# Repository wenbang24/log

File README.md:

# Log
A low-profile, wireless, portable rendition of the OLKB Planck keyboard.

# Firmware
Log uses [ZMK](https://zmk.dev/) for its firmware. The firmware is available in the `zmk-keyboard-log` sub-repo.

# BOM
| Part | Quantity | Price | Link |
| ---- | -------- | ----- | ---- |
| Supermini nRF52840 | 1 | $4.45 | [AliExpress](https://www.aliexpress.com/item/1005007205026373.html) |
| Kailh Choc V1 | 48 | $21.77 | [AliExpress](https://www.aliexpress.com/item/1005004106505158.html) |
| 1N4148 Diode | 48 | included in PCB cost | [AliExpress](https://www.aliexpress.com/item/1005003208856262.html) |
| CFX Keycap Set | 1 | $27.76 | [AliExpress](https://www.aliexpress.com/item/1005005291084816.html) |
| M2x3 Heat-Set Inserts | 4 | $1.60 | [AliExpress](https://www.aliexpress.com/item/1005003582355741.html) |
| M2 Flat Head Screws 5mm | 4 | $1.25 | [AliExpress](https://www.aliexpress.com/item/1005008691176275.html) |
| 3.7V 5000mAh Battery | 1 | $9.64 | [AliExpress](https://www.aliexpress.com/item/1005006877616182.html) |

Total: $67.83

(prices converted from AUD to USD, as of 2025-07-16)

PCB & PCBA cost: $29.34

**TOTAL: $97.17**

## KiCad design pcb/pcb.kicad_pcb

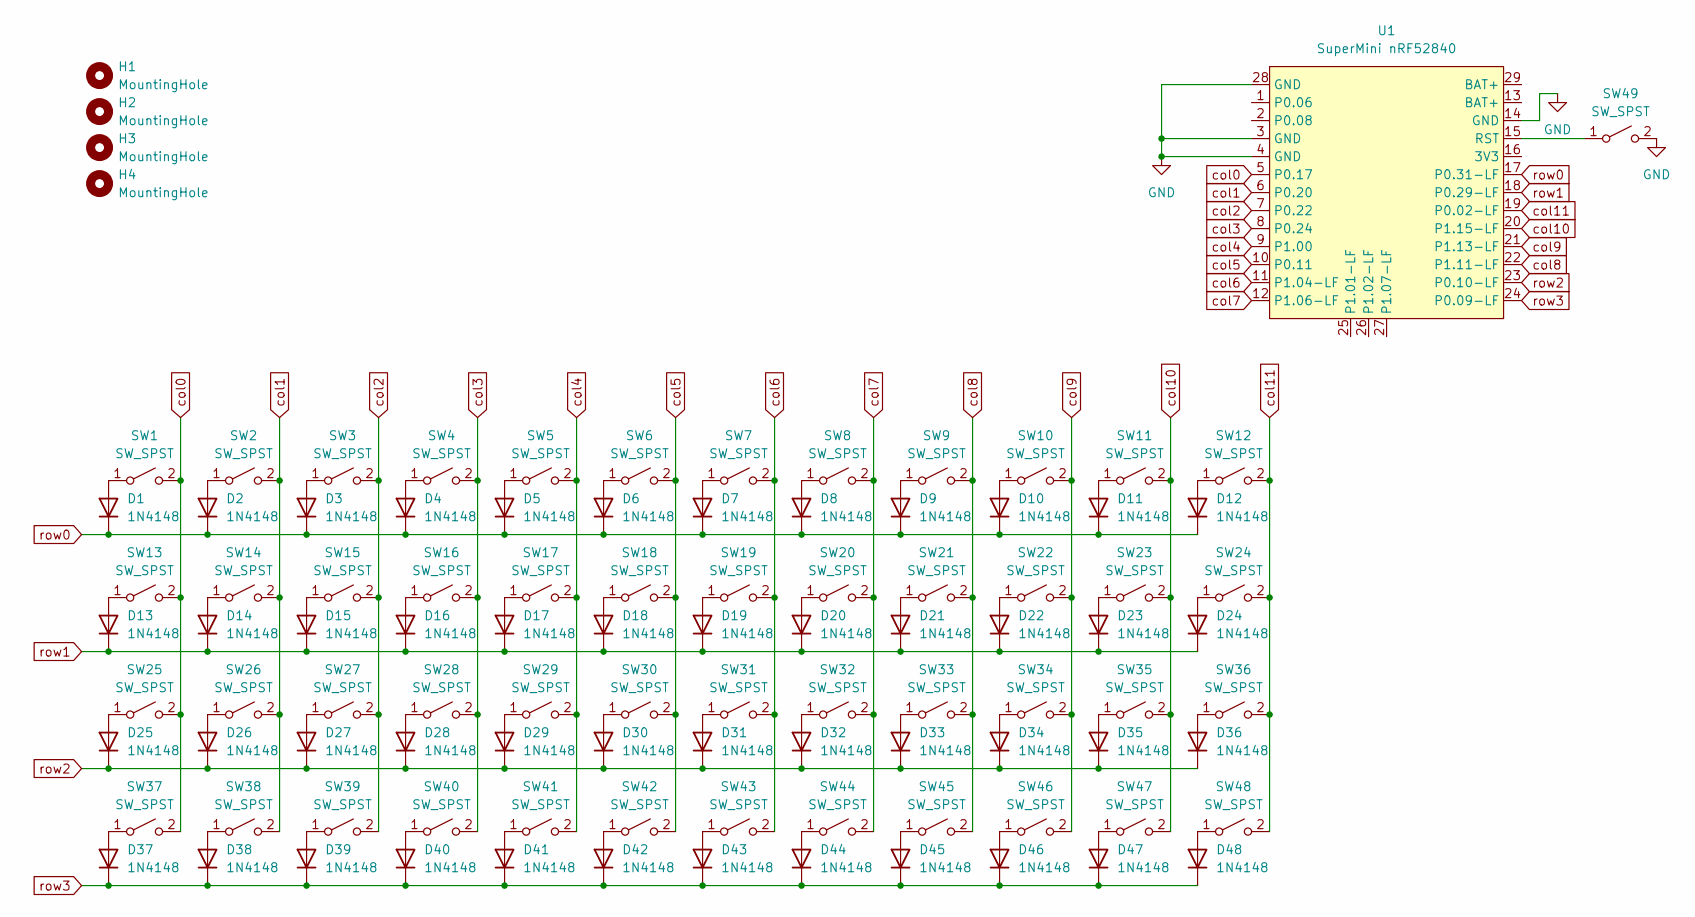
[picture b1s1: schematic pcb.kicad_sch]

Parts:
D1, D2, D3, D4, D5, D6, D7, D8, D9, D10, D11, D12, D13, D14, D15, D16, D17, D18, D19, D20, D21, D22, D23, D24, D25, D26, D27, D28, D29, D30, D31, D32, D33, D34, D35, D36, D37, D38, D39, D40, D41, D42, D43, D44, D45, D46, D47, D48: 1N4148; D_SOD-123; LCSC C81598
H1, H2, H3, H4: MountingHole; MountingHole_2.2mm_M2
SW1, SW2, SW3, SW4, SW5, SW6, SW7, SW8, SW9, SW10, SW11, SW12, SW13, SW14, SW15, SW16, SW17, SW18, SW19, SW20, SW21, SW22, SW23, SW24, SW25, SW26, SW27, SW28, SW29, SW30, SW31, SW32, SW33, SW34, SW35, SW36, SW37, SW38, SW39, SW40, SW41, SW42, SW43, SW44, SW45, SW46, SW47, SW48: SW_SPST; SW_PG1350
SW49: SW_SPST; SW_TS-1088-AR02016; LCSC C720477
U1: SuperMini nRF52840; SuperMini_nRF52840_H_USBdn

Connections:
GND: SW49.2 (B), U1.3 (GND), U1.4 (GND), U1.14 (GND), U1.28 (GND)
unnamed: D1.2 (A), SW1.1 (A)
unnamed: D2.2 (A), SW2.1 (A)
unnamed: D3.2 (A), SW3.1 (A)
unnamed: D4.2 (A), SW4.1 (A)
unnamed: D5.2 (A), SW5.1 (A)
unnamed: D6.2 (A), SW6.1 (A)
unnamed: D7.2 (A), SW7.1 (A)
unnamed: D8.2 (A), SW8.1 (A)
unnamed: D9.2 (A), SW9.1 (A)
unnamed: D10.2 (A), SW10.1 (A)
unnamed: D11.2 (A), SW11.1 (A)
unnamed: D12.2 (A), SW12.1 (A)
unnamed: D13.2 (A), SW13.1 (A)
unnamed: D14.2 (A), SW14.1 (A)
unnamed: D15.2 (A), SW15.1 (A)
unnamed: D16.2 (A), SW16.1 (A)
unnamed: D17.2 (A), SW17.1 (A)
unnamed: D18.2 (A), SW18.1 (A)
unnamed: D19.2 (A), SW19.1 (A)
unnamed: D20.2 (A), SW20.1 (A)
unnamed: D21.2 (A), SW21.1 (A)
unnamed: D22.2 (A), SW22.1 (A)
unnamed: D23.2 (A), SW23.1 (A)
unnamed: D24.2 (A), SW24.1 (A)
unnamed: D25.2 (A), SW25.1 (A)
unnamed: D26.2 (A), SW26.1 (A)
unnamed: D27.2 (A), SW27.1 (A)
unnamed: D28.2 (A), SW28.1 (A)
unnamed: D29.2 (A), SW29.1 (A)
unnamed: D30.2 (A), SW30.1 (A)
unnamed: D31.2 (A), SW31.1 (A)
unnamed: D32.2 (A), SW32.1 (A)
unnamed: D33.2 (A), SW33.1 (A)
unnamed: D34.2 (A), SW34.1 (A)
unnamed: D35.2 (A), SW35.1 (A)
unnamed: D36.2 (A), SW36.1 (A)
unnamed: D37.2 (A), SW37.1 (A)
unnamed: D38.2 (A), SW38.1 (A)
unnamed: D39.2 (A), SW39.1 (A)
unnamed: D40.2 (A), SW40.1 (A)
unnamed: D41.2 (A), SW41.1 (A)
unnamed: D42.2 (A), SW42.1 (A)
unnamed: D43.2 (A), SW43.1 (A)
unnamed: D44.2 (A), SW44.1 (A)
unnamed: D45.2 (A), SW45.1 (A)
unnamed: D46.2 (A), SW46.1 (A)
unnamed: D47.2 (A), SW47.1 (A)
unnamed: D48.2 (A), SW48.1 (A)
unnamed: SW49.1 (A), U1.15 (RST)
col0: SW1.2 (B), SW13.2 (B), SW25.2 (B), SW37.2 (B), U1.5 (P0.17)
col1: SW2.2 (B), SW14.2 (B), SW26.2 (B), SW38.2 (B), U1.6 (P0.20)
col2: SW3.2 (B), SW15.2 (B), SW27.2 (B), SW39.2 (B), U1.7 (P0.22)
col3: SW4.2 (B), SW16.2 (B), SW28.2 (B), SW40.2 (B), U1.8 (P0.24)
col4: SW5.2 (B), SW17.2 (B), SW29.2 (B), SW41.2 (B), U1.9 (P1.00)
col5: SW6.2 (B), SW18.2 (B), SW30.2 (B), SW42.2 (B), U1.10 (P0.11)
col6: SW7.2 (B), SW19.2 (B), SW31.2 (B), SW43.2 (B), U1.11 (P1.04-LF)
col7: SW8.2 (B), SW20.2 (B), SW32.2 (B), SW44.2 (B), U1.12 (P1.06-LF)
col8: SW9.2 (B), SW21.2 (B), SW33.2 (B), SW45.2 (B), U1.22 (P1.11-LF)
col9: SW10.2 (B), SW22.2 (B), SW34.2 (B), SW46.2 (B), U1.21 (P1.13-LF)
col10: SW11.2 (B), SW23.2 (B), SW35.2 (B), SW47.2 (B), U1.20 (P1.15-LF)
col11: SW12.2 (B), SW24.2 (B), SW36.2 (B), SW48.2 (B), U1.19 (P0.02-LF)
row0: D1.1 (K), D2.1 (K), D3.1 (K), D4.1 (K), D5.1 (K), D6.1 (K), D7.1 (K), D8.1 (K), D9.1 (K), D10.1 (K), D11.1 (K), D12.1 (K), U1.17 (P0.31-LF)
row1: D13.1 (K), D14.1 (K), D15.1 (K), D16.1 (K), D17.1 (K), D18.1 (K), D19.1 (K), D20.1 (K), D21.1 (K), D22.1 (K), D23.1 (K), D24.1 (K), U1.18 (P0.29-LF)
row2: D25.1 (K), D26.1 (K), D27.1 (K), D28.1 (K), D29.1 (K), D30.1 (K), D31.1 (K), D32.1 (K), D33.1 (K), D34.1 (K), D35.1 (K), D36.1 (K), U1.23 (P0.10-LF)
row3: D37.1 (K), D38.1 (K), D39.1 (K), D40.1 (K), D41.1 (K), D42.1 (K), D43.1 (K), D44.1 (K), D45.1 (K), D46.1 (K), D47.1 (K), D48.1 (K), U1.24 (P0.09-LF)

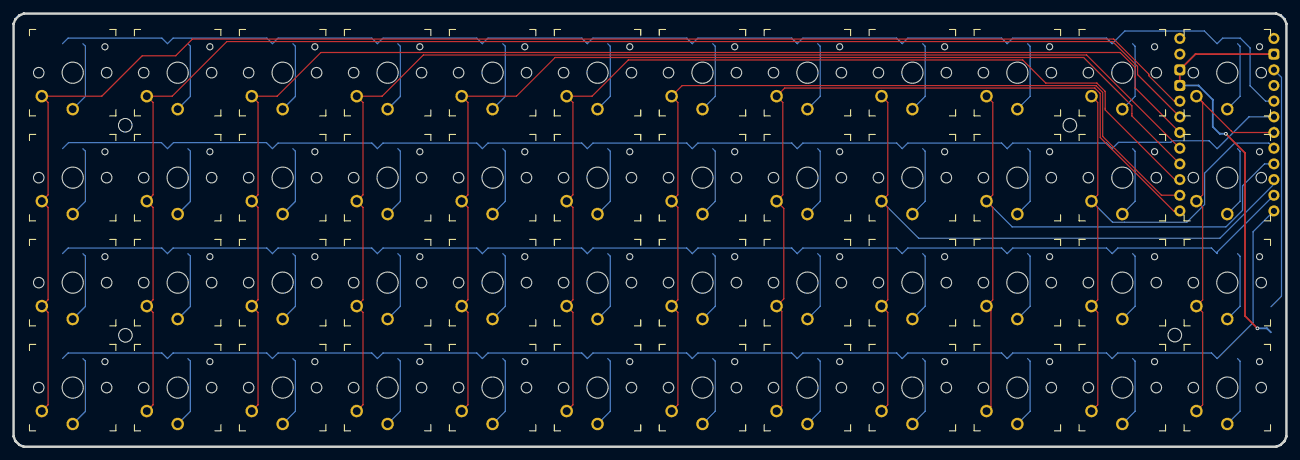
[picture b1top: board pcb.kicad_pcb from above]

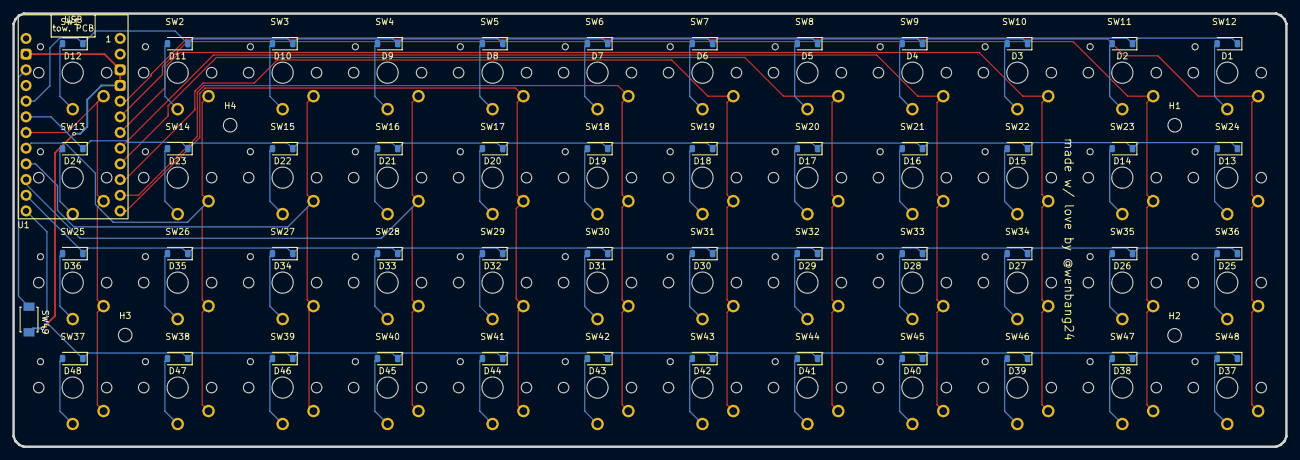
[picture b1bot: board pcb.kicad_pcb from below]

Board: 2 copper layers, 206.1 x 70.2 mm, 102 parts (50 on the bottom side), 66 nets.

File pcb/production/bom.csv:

Designator,Footprint,Quantity,Value,LCSC Part #
"D1, D10, D11, D12, D13, D14, D15, D16, D17, D18, D19, D2, D20, D21, D22, D23, D24, D25, D26, D27, D28, D29, D3, D30, D31, D32, D33, D34, D35, D36, D37, D38, D39, D4, D40, D41, D42, D43, D44, D45, D46, D47, D48, D5, D6, D7, D8, D9",D_SOD-123,48,1N4148,C81598
"SW1, SW10, SW11, SW12, SW13, SW14, SW15, SW16, SW17, SW18, SW19, SW2, SW20, SW21, SW22, SW23, SW24, SW25, SW26, SW27, SW28, SW29, SW3, SW30, SW31, SW32, SW33, SW34, SW35, SW36, SW37, SW38, SW39, SW4, SW40, SW41, SW42, SW43, SW44, SW45, SW46, SW47, SW48, SW5, SW6, SW7, SW8, SW9",SW_PG1350,48,SW_SPST,
SW49,SW_TS-1088-AR02016,1,SW_SPST,C720477

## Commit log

2025-07-06 submodules
2025-07-10 initial pcb
2025-07-11 pcb v1 done
2025-07-11 [ImgBot] Optimize images
    *Total -- 559.60kb -> 210.82kb (62.33%)
    /img/schematicv1.png -- 147.46kb -> 37.50kb (74.57%)
    /img/pcbv1.png -- 412.14kb -> 173.31kb (57.95%)
2025-07-13 small schematic changes
2025-07-13 keymap
2025-07-13 journal
2025-07-13 firmware completed & CFX spacing
2025-07-15 holes and cases
2025-07-16 BOM & render
2025-07-16 add bom to root
2025-07-16 render, bom, finishing touches'
2025-07-16 finishing touches
2025-07-16 more photos
2025-07-16 [ImgBot] Optimize images
    *Total -- 8,566.06kb -> 4,526.00kb (47.16%)
    /img/schematicv1.png -- 147.46kb -> 37.50kb (74.57%)
    /img/schematicv1.1.png -- 181.38kb -> 49.17kb (72.89%)
    /img/pcbv2.2_2.png -- 565.35kb -> 226.89kb (59.87%)
    /img/pcbv2.png -- 471.32kb -> 190.47kb (59.59%)
    /img/pcbv2.1_3.png -- 495.99kb -> 201.97kb (59.28%)
2025-07-27 prod folder
2025-07-27 wrong bom
2025-07-27 new bom
2025-07-28 render
2025-07-28 total time
2025-08-07 add pcb to readme
2025-08-07 add shipping cost
